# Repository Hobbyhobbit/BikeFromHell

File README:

see the project documentation which can be found at

http://people.ee.ethz.ch/~andstein/bfh/

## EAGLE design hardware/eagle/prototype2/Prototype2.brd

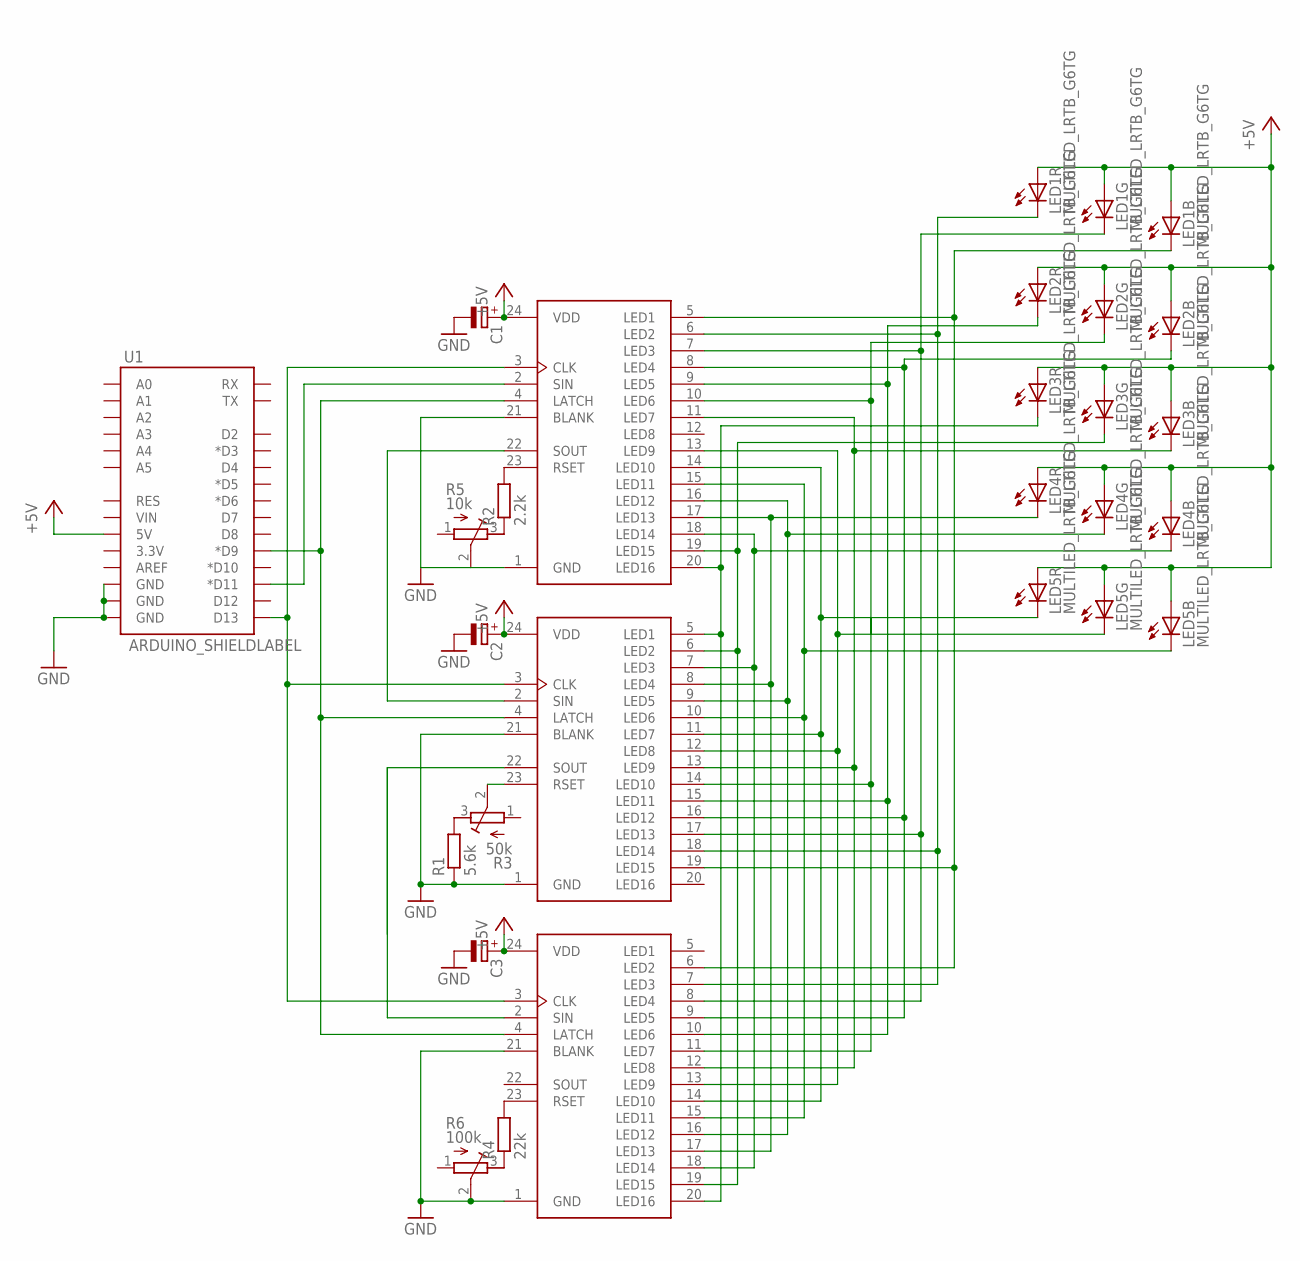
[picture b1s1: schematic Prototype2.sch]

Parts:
C1, C2, C3: CPOL-EUA/3216-18W; A/3216-18W
LED1, LED2, LED3, LED4, LED5: MULTILED_LRTB_G6TG; P-LCC-6_TOPLED
R1: 5.6k; 0204/7
R2: 2.2k; 0204/7
R3: 50k; RTRIM3165W
R4: 22k; 0204/7
R5: 10k; RTRIM3165W
R6: 100k; RTRIM3165W
U1: ARDUINO_SHIELDLABEL; DUEMILANOVE_SHIELD
U$1, U$2, U$3: CAT4016; SOIC24W

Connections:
+5V: C1.+, C2.+, C3.+, LED1.A1 (A), LED1.A2 (A), LED1.A3 (A), LED2.A1 (A), LED2.A2 (A), LED2.A3 (A), LED3.A1 (A), LED3.A2 (A), LED3.A3 (A), LED4.A1 (A), LED4.A2 (A), LED4.A3 (A), LED5.A1 (A), LED5.A2 (A), LED5.A3 (A), U1.5V, U$1.24 (VDD), U$2.24 (VDD), U$3.24 (VDD)
GND: C1.-, C2.-, C3.-, R1.1, R5.2 (S), R6.2 (S), U1.GND@0 (GND), U1.GND@1 (GND), U1.GND@2 (GND), U$1.1 (GND), U$1.21 (BLANK), U$2.1 (GND), U$2.21 (BLANK), U$3.1 (GND), U$3.21 (BLANK)
unnamed: R2.2, U$3.23 (RSET)
unnamed: R2.1, R5.3 (E)
unnamed: R4.2, U$2.23 (RSET)
unnamed: U$1.2 (SIN), U$3.22 (SOUT)
unnamed: U1.D11 (*D11), U$3.2 (SIN)
unnamed: U1.D9 (*D9), U$1.4 (LATCH), U$2.4 (LATCH), U$3.4 (LATCH)
unnamed: R4.1, R6.3 (E)
unnamed: R1.2, R3.3 (E)
unnamed: R3.2 (S), U$1.23 (RSET)
unnamed: U$1.22 (SOUT), U$2.2 (SIN)
unnamed: U1.D13, U$1.3 (CLK), U$2.3 (CLK), U$3.3 (CLK)
unnamed: LED5.C2 (C), U$1.12 (LED8), U$2.13 (LED9), U$3.13 (LED9)
unnamed: LED5.C1 (C), U$1.11 (LED7), U$2.14 (LED10), U$3.14 (LED10)
unnamed: LED5.C3 (C), U$1.10 (LED6), U$2.15 (LED11), U$3.15 (LED11)
unnamed: LED4.C2 (C), U$1.9 (LED5), U$2.16 (LED12), U$3.16 (LED12)
unnamed: LED4.C1 (C), U$1.8 (LED4), U$2.17 (LED13), U$3.17 (LED13)
unnamed: LED4.C3 (C), U$1.7 (LED3), U$2.18 (LED14), U$3.18 (LED14)
unnamed: LED3.C2 (C), U$1.6 (LED2), U$2.19 (LED15), U$3.19 (LED15)
unnamed: LED3.C3 (C), U$1.13 (LED9), U$2.12 (LED8), U$3.11 (LED7)
unnamed: LED2.C2 (C), U$1.14 (LED10), U$2.11 (LED7), U$3.10 (LED6)
unnamed: LED2.C1 (C), U$1.15 (LED11), U$2.10 (LED6), U$3.9 (LED5)
unnamed: LED2.C3 (C), U$1.16 (LED12), U$2.9 (LED5), U$3.8 (LED4)
unnamed: LED1.C2 (C), U$1.17 (LED13), U$2.8 (LED4), U$3.7 (LED3)
unnamed: LED1.C1 (C), U$1.18 (LED14), U$2.7 (LED3), U$3.6 (LED2)
unnamed: LED1.C3 (C), U$1.19 (LED15), U$2.6 (LED2), U$3.5 (LED1)
unnamed: LED3.C1 (C), U$1.5 (LED1), U$2.20 (LED16), U$3.20 (LED16)

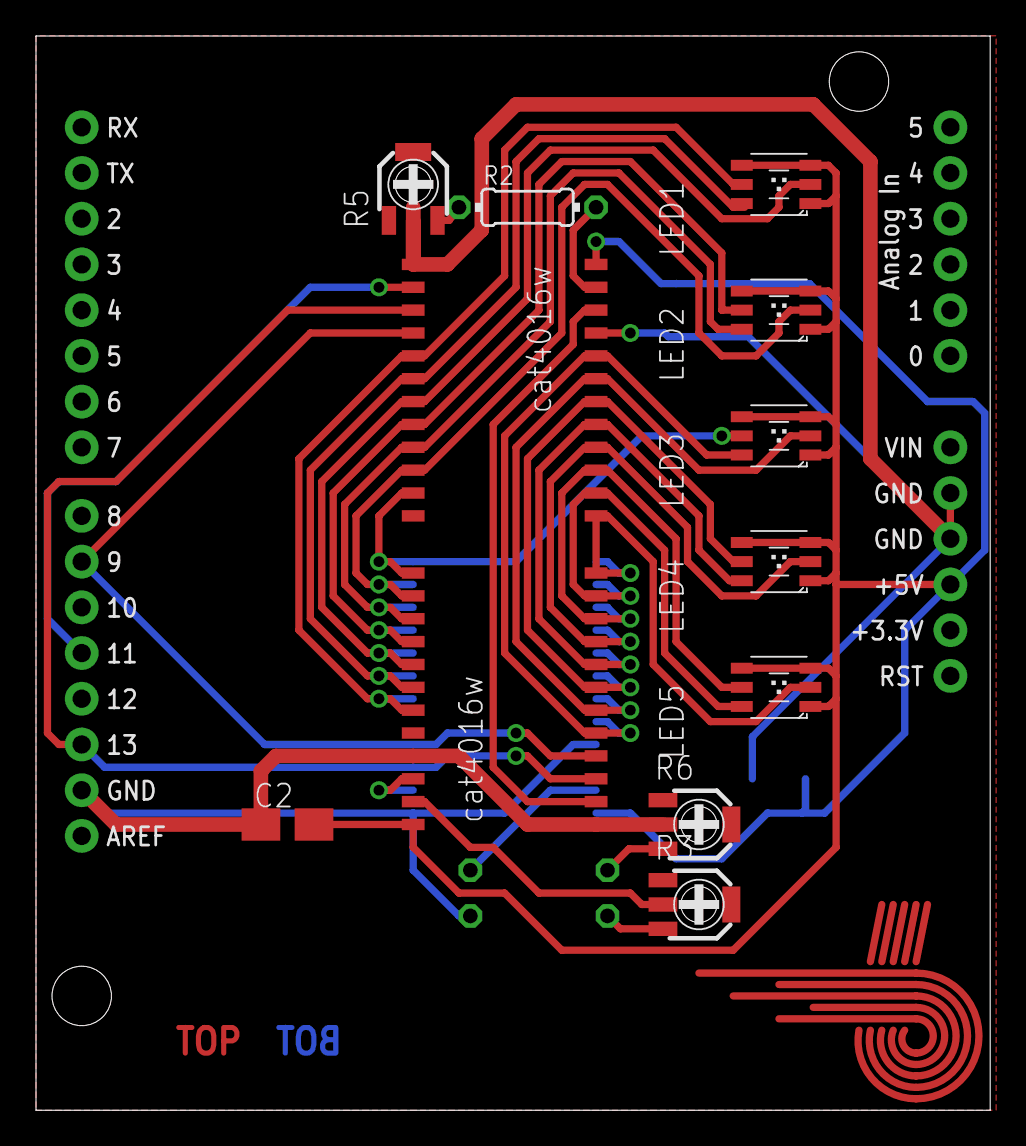
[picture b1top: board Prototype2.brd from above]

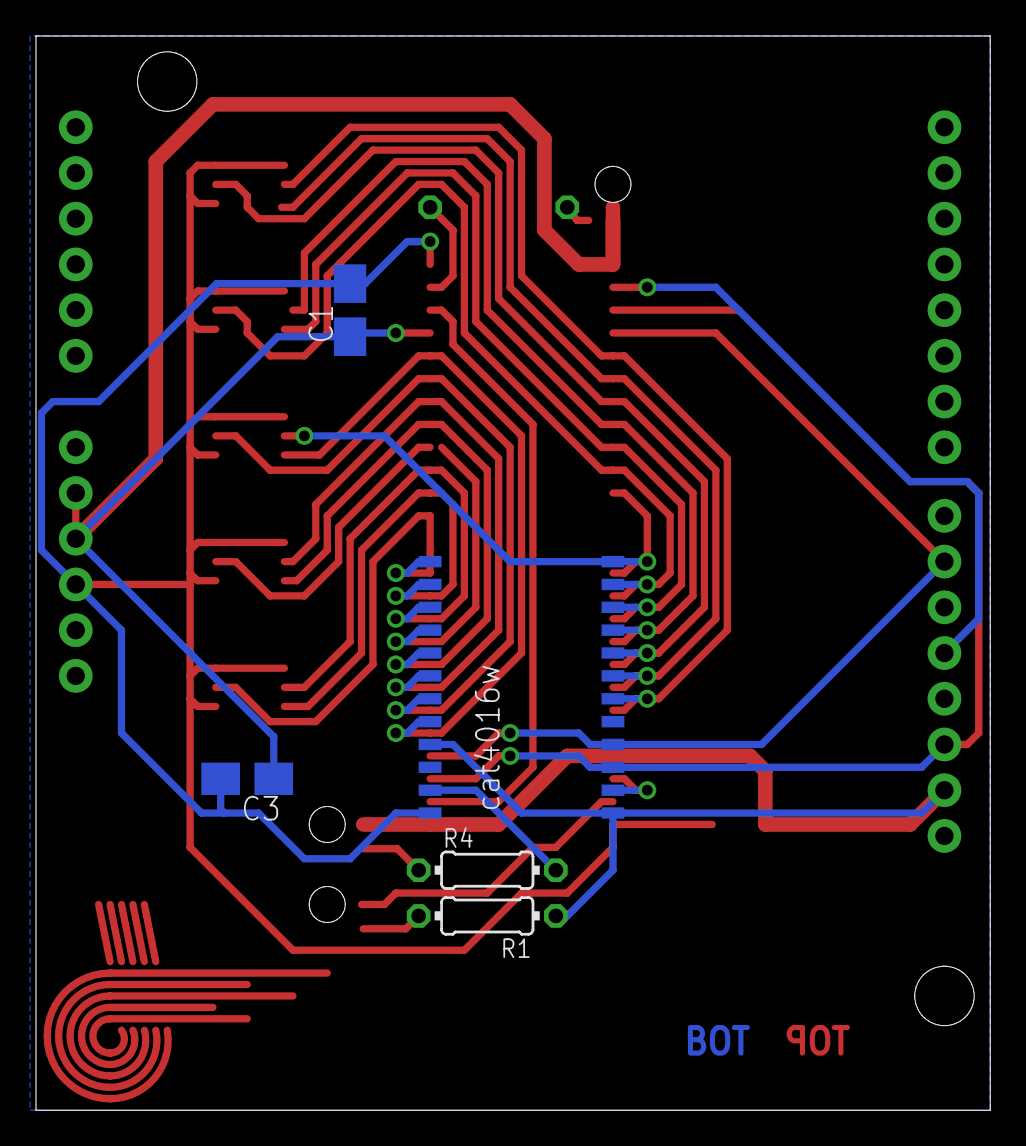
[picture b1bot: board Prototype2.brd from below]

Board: 2 copper layers, 53.0 x 59.7 mm, 18 parts (5 on the bottom side), 28 nets.

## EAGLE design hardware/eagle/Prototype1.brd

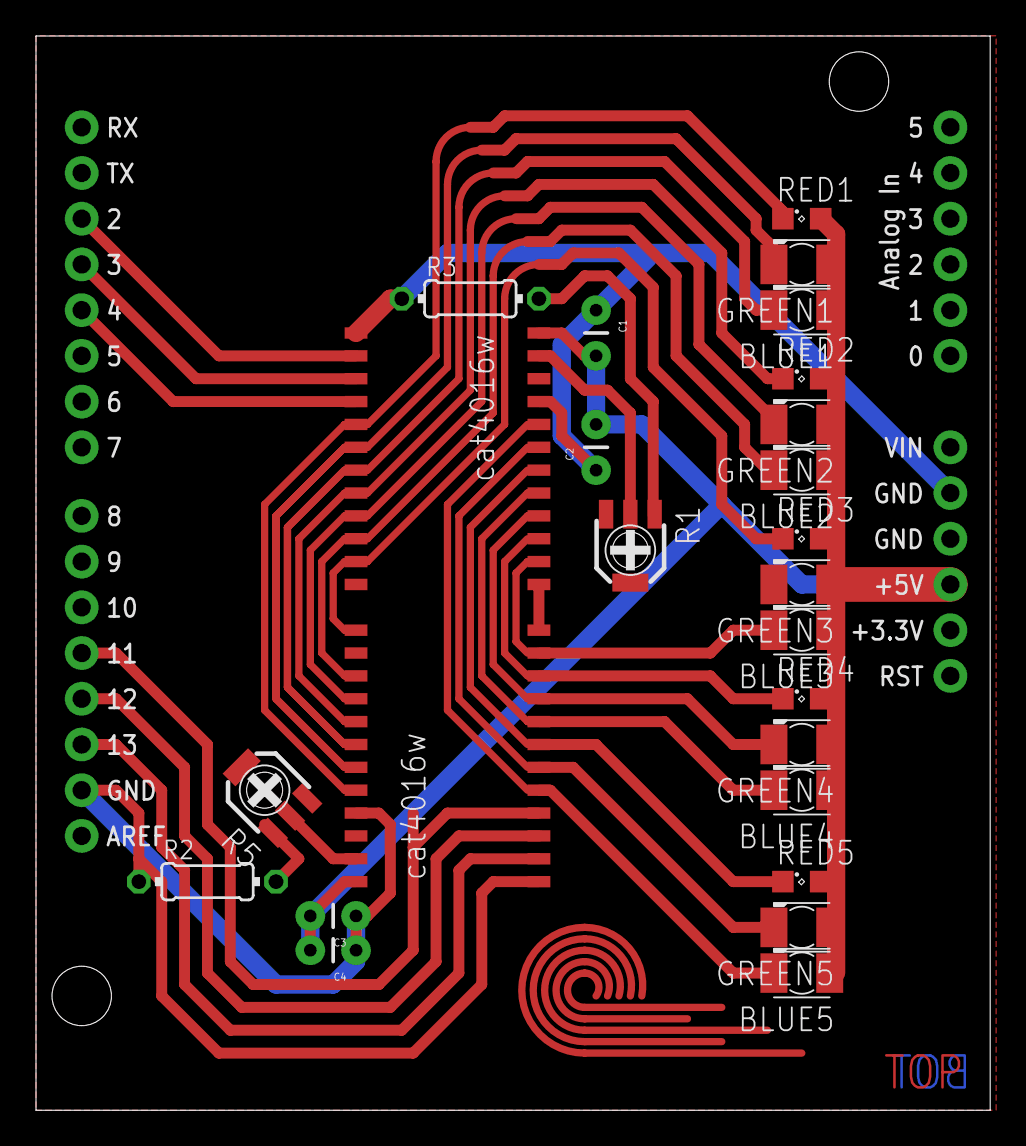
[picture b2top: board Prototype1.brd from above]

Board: 2 copper layers, 53.0 x 59.7 mm, 26 parts (0 on the bottom side), 27 nets.

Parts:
BLUE1, BLUE2, BLUE3, BLUE4, BLUE5: KA-3528ASYC
C1, C2, C3, C4: 500nF; CAP-PTH-SMALL
GREEN1, GREEN2, GREEN3, GREEN4, GREEN5: KA-3528ASYC
R1, R5: RTRIM3165W
R2, R3: 0204/7
RED1, RED2, RED3, RED4, RED5: SML0805
U1: ARDUINO_SHIELDLABEL; DUEMILANOVE_SHIELD
U$2, U$3: CAT4016; SOIC24W

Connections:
+5V: BLUE1.A, BLUE2.A, BLUE3.A, BLUE4.A, BLUE5.A, C1.2, C2.2, C3.2, C4.2, GREEN1.A, GREEN2.A, GREEN3.A, GREEN4.A, GREEN5.A, RED1.A, RED2.A, RED3.A, RED4.A, RED5.A, U1.5V, U$2.24, U$3.24
GND: C1.1, C2.1, C3.1, C4.1, R2.1, R3.1, U1.GND@0, U1.GND@1, U1.GND@2, U$2.1, U$2.21, U$3.1, U$3.21
unnamed: R1.1, R3.2
unnamed: R2.2, R5.1
unnamed: R1.2, U$2.23
unnamed: R5.2, U$3.23
unnamed: U1.D3, U$2.3
unnamed: U1.D4, U$2.4
unnamed: U1.D13, U$3.2
unnamed: U1.D2, U$2.2
unnamed: GREEN2.C, U$2.9, U$3.16
unnamed: RED2.C, U$2.8, U$3.17
unnamed: BLUE1.C, U$2.7, U$3.18
unnamed: GREEN1.C, U$2.6, U$3.19
unnamed: BLUE2.C, U$2.10, U$3.15
unnamed: RED1.C, U$2.5, U$3.20
unnamed: RED3.C, U$2.11, U$3.13
unnamed: GREEN3.C, U$2.13, U$3.12
unnamed: BLUE3.C, U$2.14, U$3.11
unnamed: RED4.C, U$2.15, U$3.10
unnamed: GREEN4.C, U$2.16, U$3.9
unnamed: BLUE4.C, U$2.17, U$3.8
unnamed: RED5.C, U$2.18, U$3.7
unnamed: GREEN5.C, U$2.19, U$3.6
unnamed: U1.D12, U$3.3
unnamed: U1.D11, U$3.4
unnamed: BLUE5.C, U$2.20, U$3.5

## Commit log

2012-01-31 /patterns
2012-01-31 Durchsucht Ordner für Dateiliste
2012-01-31 +Lost_slots.matrix
2012-02-01 LEDs can be changed on-the-fly; atom.matrix
    - setting dimensions from .matrix files
    - crushing colors to current setting
2012-02-01 Ein Auge.
2012-02-02 added hardware/
    - eagle
    - geda : gschem/pcb files
    - datasheets
    also added links.txt for further reference
2012-02-02 Board angefangen. Sehr kleine Leiter.
2012-02-03 included P5control lib; added "fps"
2012-02-03 cat4016 hat nun kleine Füsse
2012-02-04 Wege bahnen WIP
2012-02-04 Wege bahnen: dateien vergsn. ups.
2012-02-04 added cheap BT module link
2012-02-05 Prototyp 1 verkabelt
2012-02-05 added artwork directory
2012-02-05 added M74HC595B datasheet
2012-02-06 logo ideas
2012-02-07 fixed pours both sides; little logo
2012-02-07 logo neu
2012-02-07 finished Prototype1, created gerber
2012-02-07 datasheet Multiled
2012-02-17 peek preview of prototype board mounted on arduino
2012-02-21 +/arduino
2012-02-25 playAround.ino: LEDs gemappt und ansteuerbar
2012-03-04 added SPI test arduino script & Makefile
    the Makefile must be edited for the local configuration
    and can be used to generate the temporary applet files;
    these are particularly interesting to see the actual
    implementation of the different provided arduino function
    for speed-debugging purposes...
2012-03-06 added OSX Arduino 1.0 Makefile
2012-03-07 new firmware that loads values from processing
    connect the shield to the USB and hit the "flash" button
    in the BikeFromHell sketch...
    (pre-alpha early release)
2012-03-07 Prototype2
2012-03-07 proto2.zip
2012-03-07 temporary commit before merge
2012-03-07 removed generated applet files
    simply restart your Makefile to re-create them...
2012-03-07 Aufräumversuch prototypeverzeichnis
2012-03-11 added Sphinx documentation
    the compiled documentation can be found at
    documentation/_build/html/index.html
2012-03-11 prototype2: resistor values, partlist
2012-03-12 Prototype2: Layout-update. doc: parts-list prototype 2
2012-03-12 Gerber files for updated Prototype2
2012-03-13 parts.rst: fixed malformed table
2012-03-13 Ignore _build
2012-03-13 updated BikeFromHell/test_serial
    processing/firmware communication now works somewhat
    more stable (though not perfectly, yet)
    more changes
    - pulsedtr.py for resetting arduino via USB
    - artwork/logo_prototype2.{png,svg}
    - bluetooth.rst
2012-03-13 removed sphinx/_build
    the documentation will be pushed on a separate place in the
    internet using a git hook...
2012-03-13 added README with link to sphinx documentation
2012-03-13 added some bluetooth references and a pinout
2012-04-06 temporary Colorpicker
2012-04-06 added more references, TCL5940 datasheet
2012-04-26 added new avr/ code
    this particularly contains a new interrupt driven protocol
    implementation; also added sketches/TestProtocol/ and changed
    sketches/BikeFromHell/serializer.pde (does not really work yet)
    beware that avr/ code is not "arduino compatible" anymore; this
    step was necessary to get the performance specifications we will
    need for the final implementation... prototyping can still be
2012-04-26 Serializer: allow no connection
2012-05-13 added simple program to test bluetooth\n\ncurrently simply echoes text (\r and/or \n compatible)
2012-05-13 enhanced bluetooth/parts documentation
2012-05-13 simple protocol implementation\n\nusing ISR for fast transfer from UART
2012-05-13 updated arduino shield schematic/footprint (geda)
2012-05-13 added some geda symbols
2012-05-13 added PCB footprint for bluetooth board & pfc.py
2012-05-13 updated .gitignore
2012-05-13 simple pin mapper for prototype2
2012-05-20 Mapping PT2
2012-07-03 moved pin_mapper to pin_mapper_1
2012-07-03 updated documentation
    added datasheets for new LED, bluetooth module information,
    new LED driver
2012-07-03 cleanup in hardware/geda
2012-07-03 added bluetooth arduino shield
2012-07-03 added draft of third prototype board
2012-07-05 added 2nd TLC to prototype3
    also changed TLC symbol (moved XLAT next to serial interface pins)
2012-07-21 update some local files
2012-09-05 updated parts.rst, added some datasheets
2012-09-05 updated prototype3.sch (hall, bt, connector)
2012-09-05 started work on prototype3.pcb
2012-11-23 partially routed prototype3
2012-11-23 added test for parts in prototype3
2012-11-24 almost finished prototype3.v1
2012-11-24 protype3.v1
2012-11-24 updated artwork; included logo into protoype3.v1
    also added brew compatible update.sh (commented by default)
2012-11-24 added gerber files protoype3v1
2012-11-26 corrected some DRC violations prototype3v1
2013-01-27 P3: Test SPI
2014-09-23 removed sphinx extension matplotlib
2014-09-23 set sphinx_rtd_theme as local sphinx theme
    to accelerate page loading, install the following google fonts:
    - Lato
    - Roboto Slab
    - Inconsolata
    (for example using SkyFont)
2014-10-28 added avr/Makefiles
2014-10-28 added some annotations YTC2/TLC5940 datasheets
2014-10-28 switched signals gsclk (oc1a->clko) / blank (clko->oc1a) on prototype3
2014-11-05 Ancient changes in Processing sketches
2014-11-05 Fixed TLC-Prototype
2014-11-05 Documentation update (speed)
2014-11-05 Hardware descriptors for Processing Interface
2014-11-05 Leftovers
2014-11-06 added compiled footprints
2014-11-06 bugfix avr/Makefile
2014-11-06 Sketch for HW-TLC

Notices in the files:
parts and their libraries:
SparkFun: Licensing: CC v3.0 Share-Alike You are welcome to use this library for commercial purposes.
